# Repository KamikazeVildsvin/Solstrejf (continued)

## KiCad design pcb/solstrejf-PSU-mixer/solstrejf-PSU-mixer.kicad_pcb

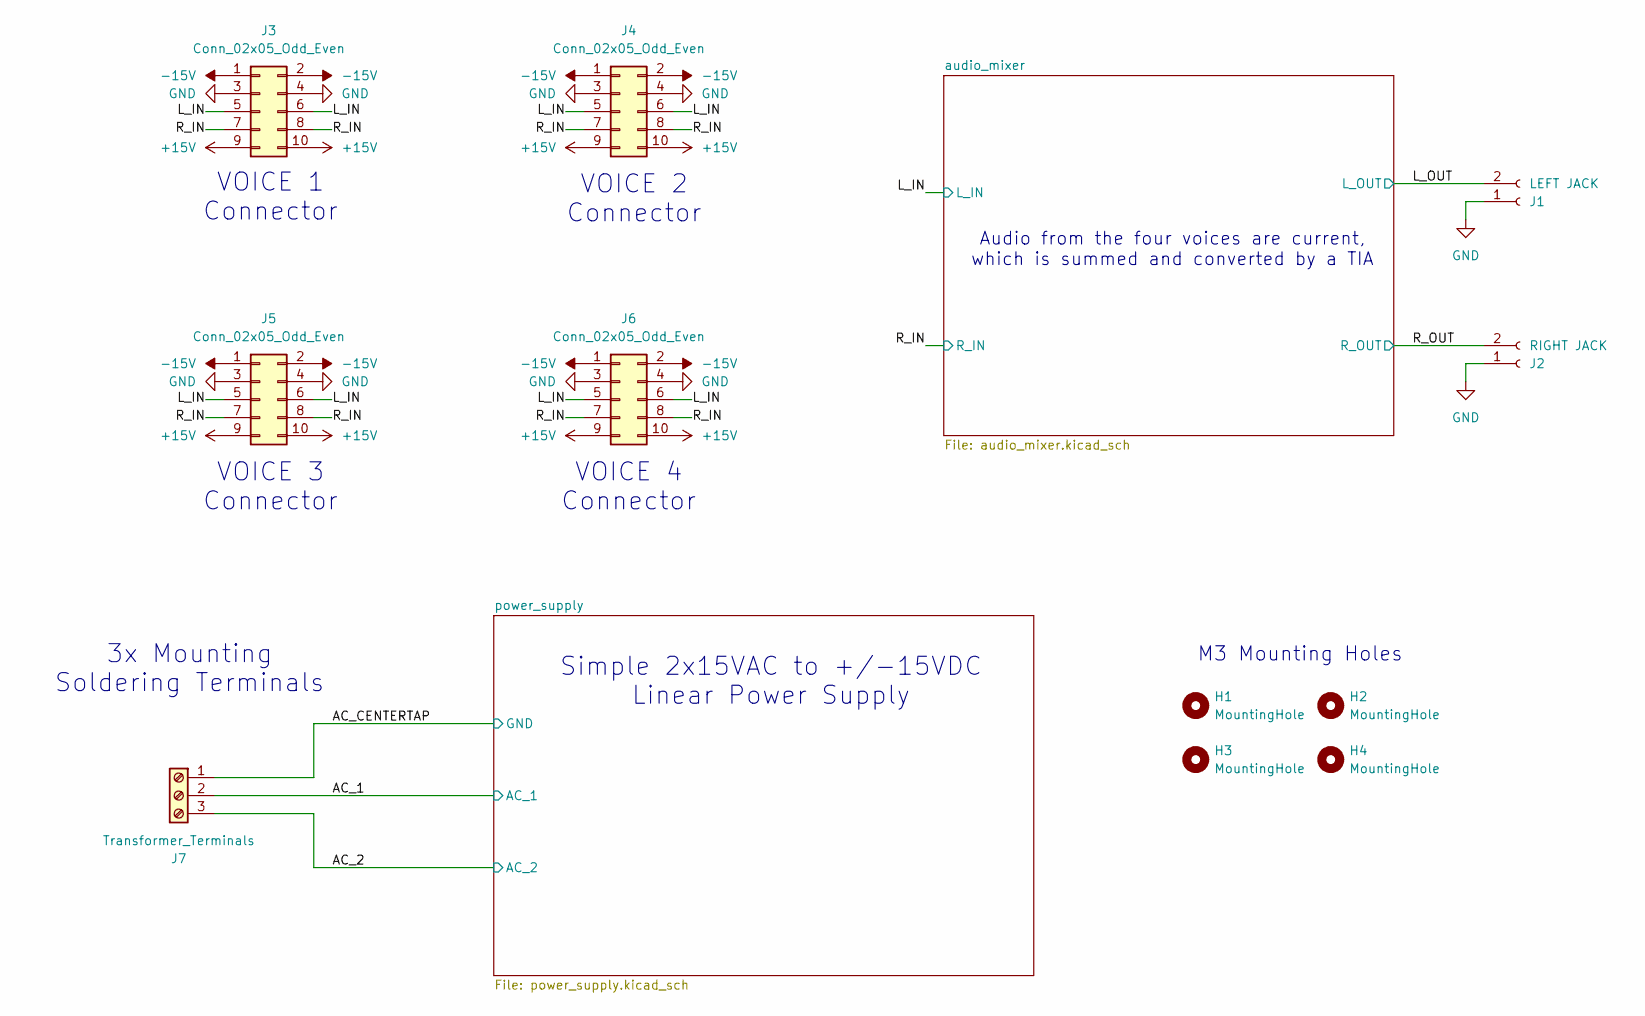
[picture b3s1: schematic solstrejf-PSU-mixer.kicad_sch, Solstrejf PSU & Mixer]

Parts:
H1, H2, H3, H4: MountingHole; MountingHole_3.2mm_M3_DIN965
J1: LEFT JACK; PinHeader_1x02_P2.54mm_Vertical
J2: RIGHT JACK; PinHeader_1x02_P2.54mm_Vertical
J3, J4, J5, J6: Conn_02x05_Odd_Even; IDC-Header_2x05_P2.54mm_Vertical
J7: Transformer_Terminals; SolderWire-0.5sqmm_1x03_P4.8mm_D0.9mm_OD2.3mm

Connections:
+15V: J3.9, J3.10, J4.9, J4.10, J5.9, J5.10, J6.9, J6.10; also elsewhere on the board
-15V: J3.1, J3.2, J4.1, J4.2, J5.1, J5.2, J6.1, J6.2; also elsewhere on the board
/AC_1: J7.2; also elsewhere on the board
/AC_2: J7.3; also elsewhere on the board
/L_IN: J3.5, J3.6, J4.5, J4.6, J5.5, J5.6, J6.5, J6.6; also elsewhere on the board
/L_OUT: J1.2; also elsewhere on the board
/R_IN: J3.7, J3.8, J4.7, J4.8, J5.7, J5.8, J6.7, J6.8; also elsewhere on the board
/R_OUT: J2.2; also elsewhere on the board
GND: J1.1, J2.1, J3.3, J3.4, J4.3, J4.4, J5.3, J5.4, J6.3, J6.4, J7.1; also elsewhere on the board

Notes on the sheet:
Audio from the four voices are current, which is summed and converted by a TIA
Simple 2x15VAC to +/-15VDC Linear Power Supply
M3 Mounting Holes
3x Mounting Soldering Terminals
VOICE 2 Connector
VOICE 1 Connector
VOICE 4 Connector
VOICE 3 Connector

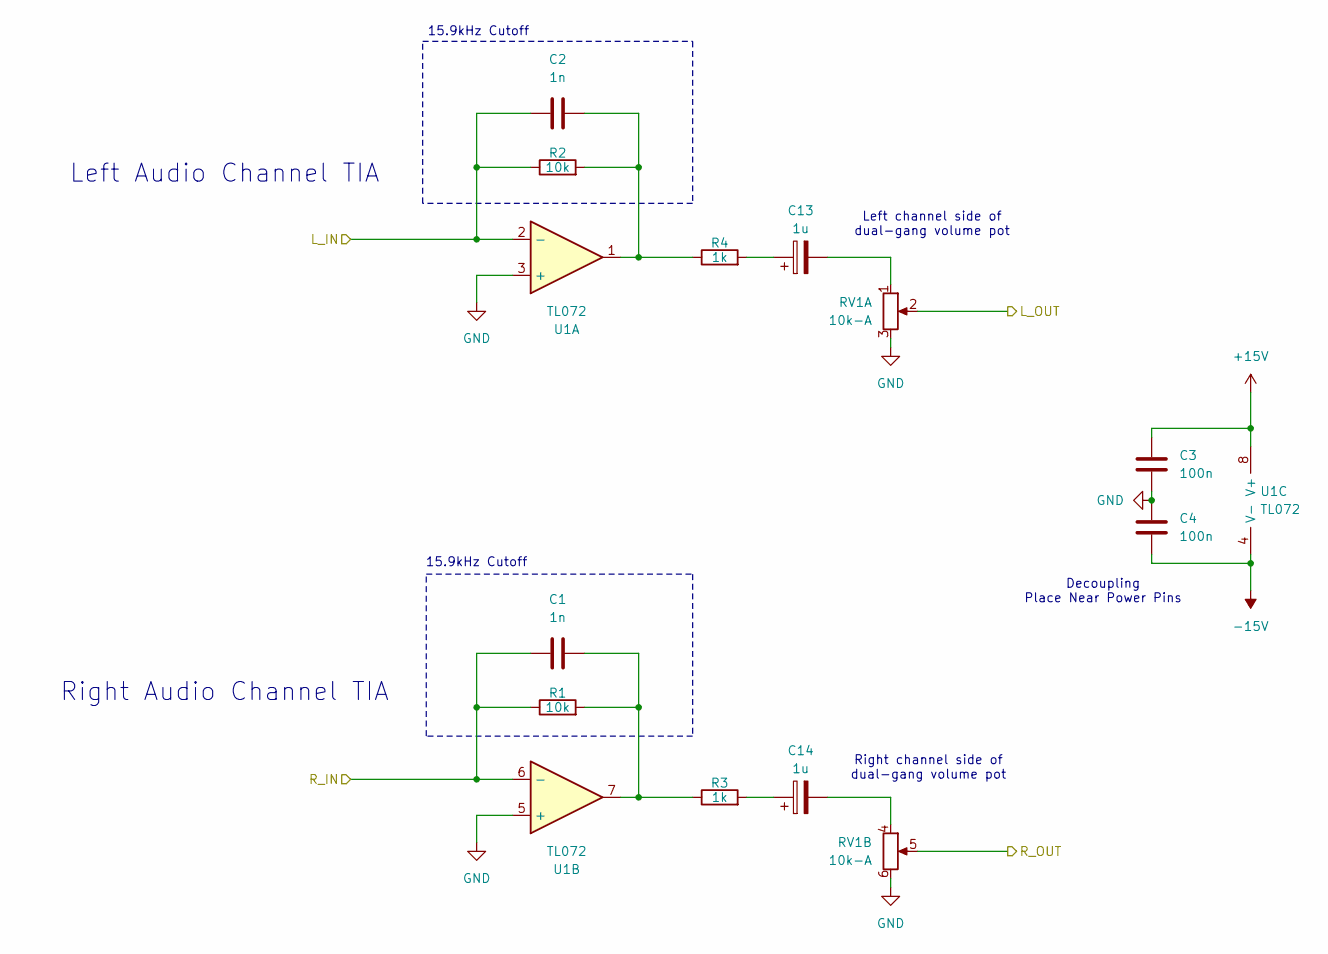
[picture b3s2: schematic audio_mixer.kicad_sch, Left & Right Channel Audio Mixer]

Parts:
C1, C2: 1n; C_Disc_D5.0mm_W2.5mm_P5.00mm
C3, C4: 100n; C_Disc_D5.0mm_W2.5mm_P5.00mm
C13, C14: 1u; CP_Radial_D5.0mm_P2.00mm
R1, R2: 10k; R_Axial_DIN0207_L6.3mm_D2.5mm_P10.16mm_Horizontal
R3, R4: 1k; R_Axial_DIN0207_L6.3mm_D2.5mm_P10.16mm_Horizontal
RV1: 10k-A; PinHeader_2x03_P2.54mm_Vertical
U1: TL072; DIP-8_W7.62mm

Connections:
+15V: C3.2, U1.8 (V+); also elsewhere on the board
-15V: C4.1, U1.4 (V-); also elsewhere on the board
/L_IN: C2.1, R2.1, U1.2 (-); also elsewhere on the board
/L_OUT: RV1.2; also elsewhere on the board
/R_IN: C1.1, R1.1, U1.6 (-); also elsewhere on the board
/R_OUT: RV1.5; also elsewhere on the board
GND: C3.1, C4.2, RV1.3, RV1.6, U1.3 (+), U1.5 (+); also elsewhere on the board
unnamed: C1.2, R1.2, R3.1, U1.7
unnamed: C2.2, R2.2, R4.1, U1.1
unnamed: C13.1, R4.2
unnamed: C13.2, RV1.1
unnamed: C14.1, R3.2
unnamed: C14.2, RV1.4

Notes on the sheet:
Decoupling Place Near Power Pins
Left Audio Channel TIA
15.9kHz Cutoff
Right Audio Channel TIA
Right channel side of dual-gang volume pot
Left channel side of dual-gang volume pot

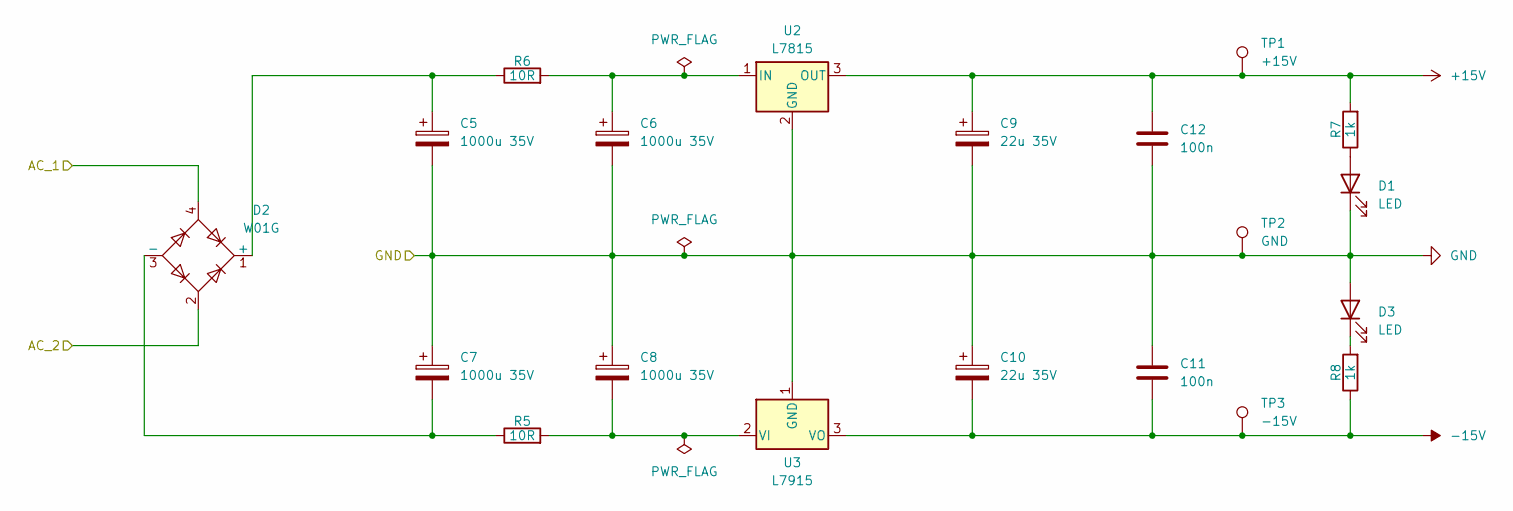
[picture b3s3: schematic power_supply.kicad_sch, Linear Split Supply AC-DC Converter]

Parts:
C5, C6, C7, C8: 1000u 35V; CP_Radial_D10.0mm_P5.00mm
C9, C10: 22u 35V; CP_Radial_D5.0mm_P2.00mm
C11, C12: 100n; C_Disc_D5.0mm_W2.5mm_P5.00mm
D1, D3: LED; LED_D5.0mm_FlatTop
D2: W01G; Diode_Bridge_Round_D9.8mm
R5, R6: 10R; R_Axial_DIN0207_L6.3mm_D2.5mm_P10.16mm_Horizontal
R7, R8: 1k; R_Axial_DIN0207_L6.3mm_D2.5mm_P10.16mm_Horizontal
TP1: +15V; PinHeader_1x01_P2.54mm_Vertical
TP2: GND; PinHeader_1x01_P2.54mm_Vertical
TP3: -15V; PinHeader_1x01_P2.54mm_Vertical
U2: L7815; TO-220-3_Vertical
U3: L7915; TO-220-3_Vertical

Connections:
+15V: C9.1, C12.2, R7.2, TP1.1, U2.3 (OUT); also elsewhere on the board
-15V: C10.2, C11.1, R8.1, TP3.1, U3.3 (VO); also elsewhere on the board
/AC_1: D2.4; also elsewhere on the board
/AC_2: D2.2; also elsewhere on the board
GND: C5.2, C6.2, C7.1, C8.1, C9.2, C10.1, C11.2, C12.1, D1.1 (K), D3.2 (A), TP2.1, U2.2 (GND), U3.1 (GND); also elsewhere on the board
unnamed: D1.2 (A), R7.1
unnamed: C5.1, D2.1 (+), R6.1
unnamed: C7.2, D2.3 (-), R5.1
unnamed: D3.1 (K), R8.2
unnamed: C6.1, R6.2, U2.1 (IN)
unnamed: C8.2, R5.2, U3.2 (VI)

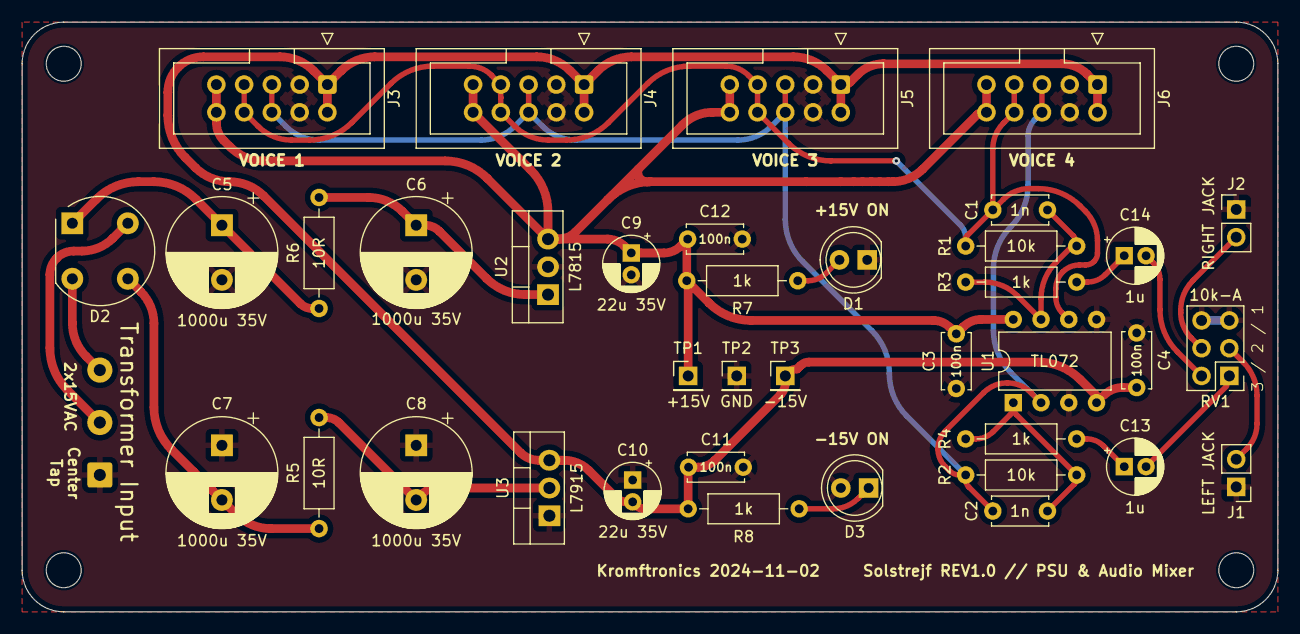
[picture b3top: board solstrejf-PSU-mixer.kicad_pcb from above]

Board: 2 copper layers, 114.9 x 54.0 mm, 43 parts (0 on the bottom side), 21 nets.

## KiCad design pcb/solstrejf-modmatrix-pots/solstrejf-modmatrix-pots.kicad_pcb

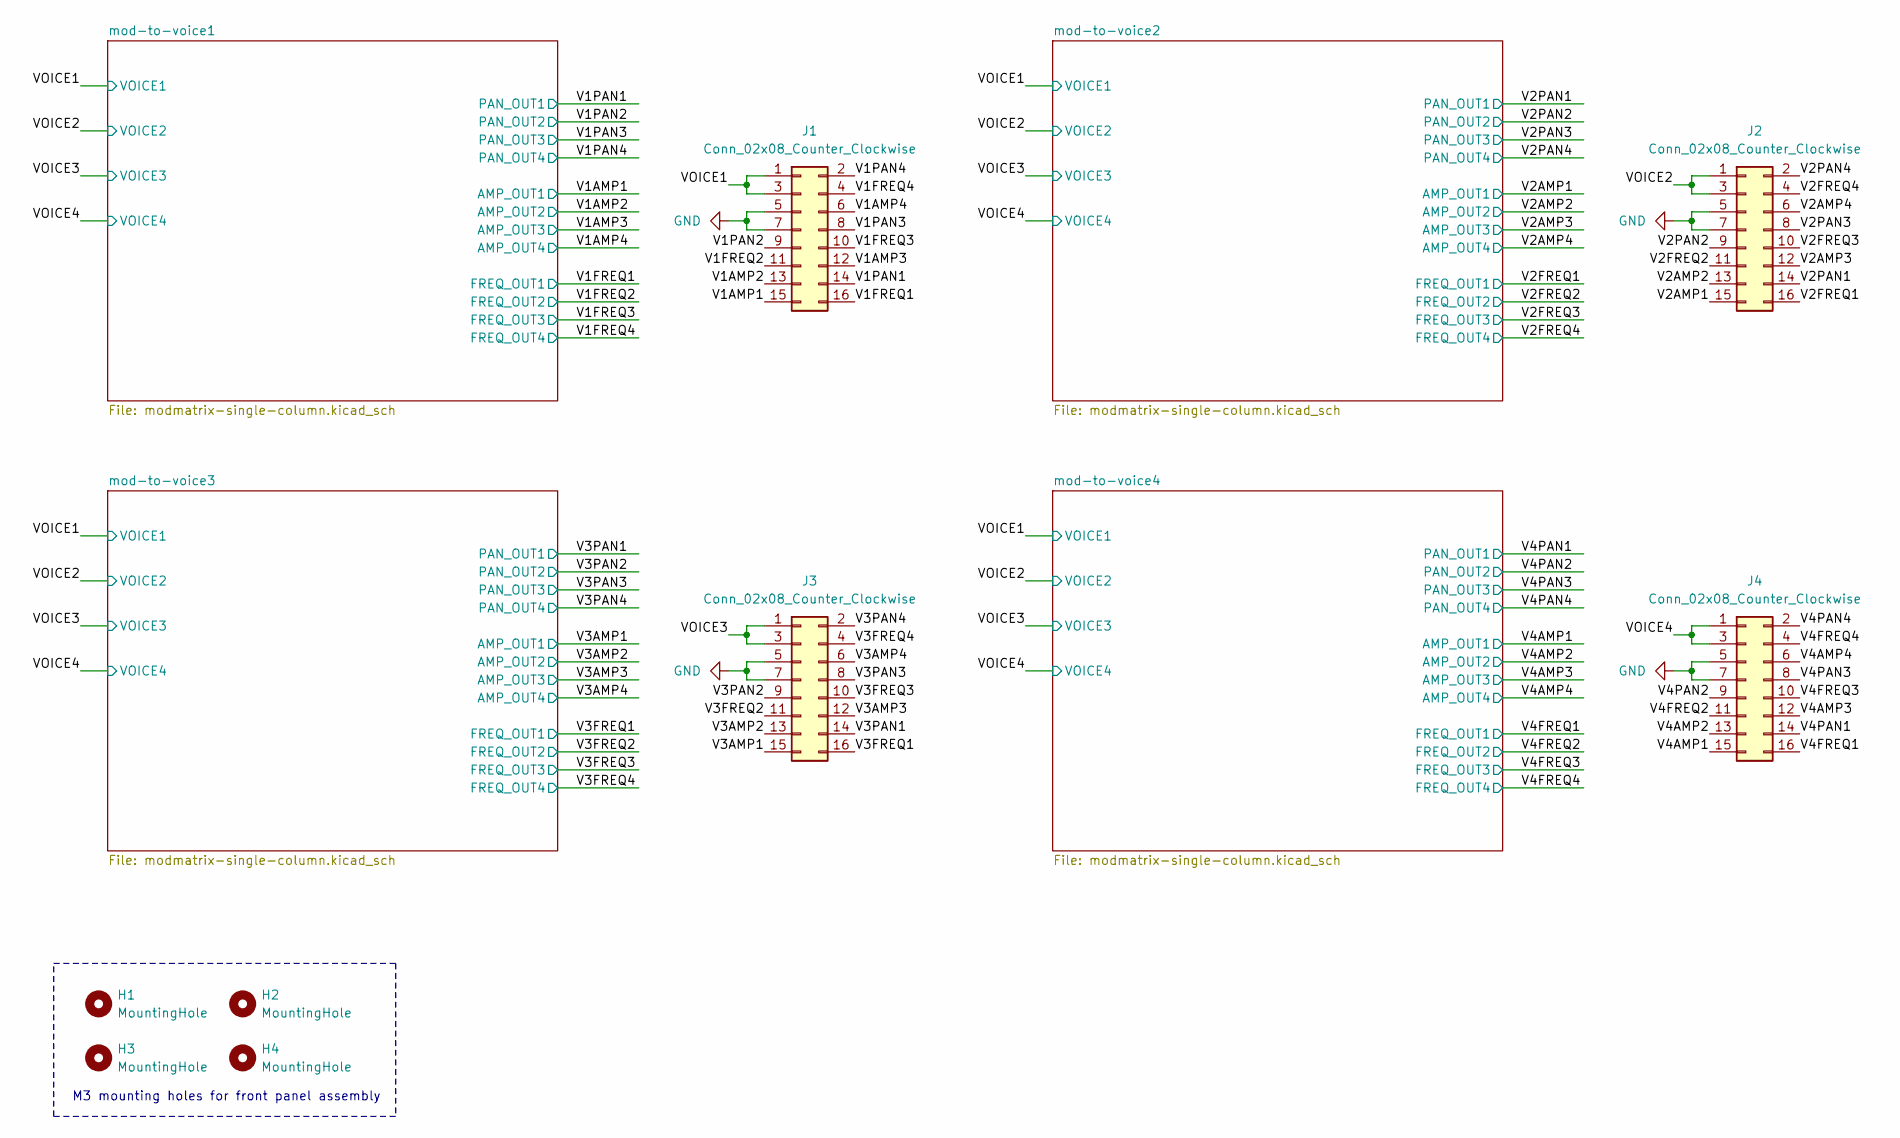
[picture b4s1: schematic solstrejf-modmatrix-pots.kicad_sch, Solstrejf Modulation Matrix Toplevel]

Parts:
H1, H2, H3, H4: MountingHole; MountingHole_3.2mm_M3_DIN965
J1, J2, J3, J4: Conn_02x08_Counter_Clockwise; IDC-Header_2x08_P2.54mm_Vertical

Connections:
/V1AMP1: J1.15; also elsewhere on the board
/V1AMP2: J1.13; also elsewhere on the board
/V1AMP3: J1.12; also elsewhere on the board
/V1AMP4: J1.6; also elsewhere on the board
/V1FREQ1: J1.16; also elsewhere on the board
/V1FREQ2: J1.11; also elsewhere on the board
/V1FREQ3: J1.10; also elsewhere on the board
/V1FREQ4: J1.4; also elsewhere on the board
/V1PAN1: J1.14; also elsewhere on the board
/V1PAN2: J1.9; also elsewhere on the board
/V1PAN3: J1.8; also elsewhere on the board
/V1PAN4: J1.2; also elsewhere on the board
/V2AMP1: J2.15; also elsewhere on the board
/V2AMP2: J2.13; also elsewhere on the board
/V2AMP3: J2.12; also elsewhere on the board
/V2AMP4: J2.6; also elsewhere on the board
/V2FREQ1: J2.16; also elsewhere on the board
/V2FREQ2: J2.11; also elsewhere on the board
/V2FREQ3: J2.10; also elsewhere on the board
/V2FREQ4: J2.4; also elsewhere on the board
/V2PAN1: J2.14; also elsewhere on the board
/V2PAN2: J2.9; also elsewhere on the board
/V2PAN3: J2.8; also elsewhere on the board
/V2PAN4: J2.2; also elsewhere on the board
/V3AMP1: J3.15; also elsewhere on the board
/V3AMP2: J3.13; also elsewhere on the board
/V3AMP3: J3.12; also elsewhere on the board
/V3AMP4: J3.6; also elsewhere on the board
/V3FREQ1: J3.16; also elsewhere on the board
/V3FREQ2: J3.11; also elsewhere on the board
/V3FREQ3: J3.10; also elsewhere on the board
/V3FREQ4: J3.4; also elsewhere on the board
/V3PAN1: J3.14; also elsewhere on the board
/V3PAN2: J3.9; also elsewhere on the board
/V3PAN3: J3.8; also elsewhere on the board
/V3PAN4: J3.2; also elsewhere on the board
/V4AMP1: J4.15; also elsewhere on the board
/V4AMP2: J4.13; also elsewhere on the board
/V4AMP3: J4.12; also elsewhere on the board
/V4AMP4: J4.6; also elsewhere on the board
/V4FREQ1: J4.16; also elsewhere on the board
/V4FREQ2: J4.11; also elsewhere on the board
/V4FREQ3: J4.10; also elsewhere on the board
/V4FREQ4: J4.4; also elsewhere on the board
/V4PAN1: J4.14; also elsewhere on the board
/V4PAN2: J4.9; also elsewhere on the board
/V4PAN3: J4.8; also elsewhere on the board
/V4PAN4: J4.2; also elsewhere on the board
/VOICE1: J1.1, J1.3; also elsewhere on the board
/VOICE2: J2.1, J2.3; also elsewhere on the board
/VOICE3: J3.1, J3.3; also elsewhere on the board
/VOICE4: J4.1, J4.3; also elsewhere on the board
GND: J1.5, J1.7, J2.5, J2.7, J3.5, J3.7, J4.5, J4.7; also elsewhere on the board

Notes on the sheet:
M3 mounting holes for front panel assembly

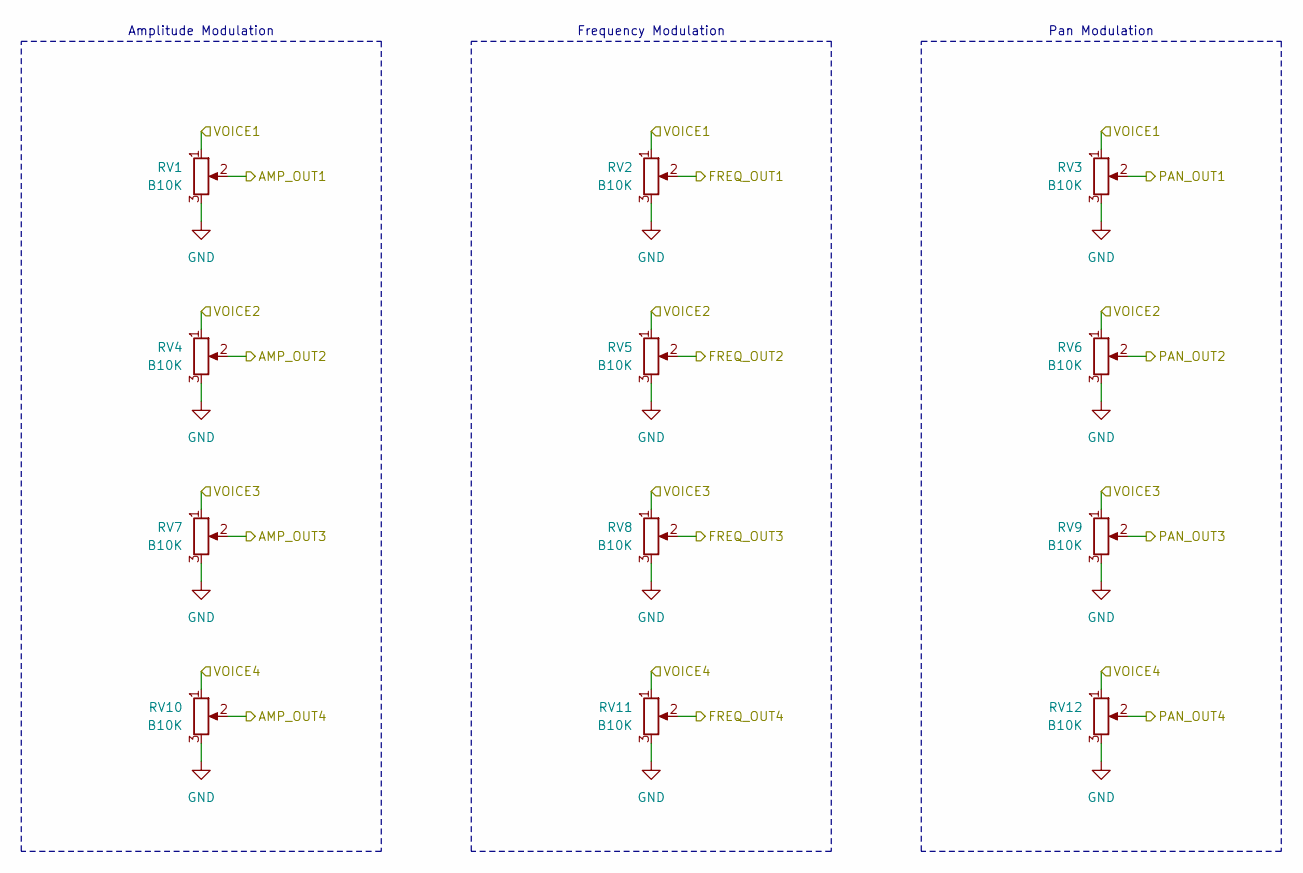
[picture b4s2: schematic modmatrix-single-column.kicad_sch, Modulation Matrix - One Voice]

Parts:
RV1, RV2, RV3, RV4, RV5, RV6, RV7, RV8, RV9, RV10, RV11, RV12: B10K; Potentiometer_Alpha_slide_pot_30mm

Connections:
/V1AMP1: RV1.2; also elsewhere on the board
/V1AMP2: RV4.2; also elsewhere on the board
/V1AMP3: RV7.2; also elsewhere on the board
/V1AMP4: RV10.2; also elsewhere on the board
/V1FREQ1: RV2.2; also elsewhere on the board
/V1FREQ2: RV5.2; also elsewhere on the board
/V1FREQ3: RV8.2; also elsewhere on the board
/V1FREQ4: RV11.2; also elsewhere on the board
/V1PAN1: RV3.2; also elsewhere on the board
/V1PAN2: RV6.2; also elsewhere on the board
/V1PAN3: RV9.2; also elsewhere on the board
/V1PAN4: RV12.2; also elsewhere on the board
/VOICE1: RV1.1, RV2.1, RV3.1; also elsewhere on the board
/VOICE2: RV4.1, RV5.1, RV6.1; also elsewhere on the board
/VOICE3: RV7.1, RV8.1, RV9.1; also elsewhere on the board
/VOICE4: RV10.1, RV11.1, RV12.1; also elsewhere on the board
GND: RV1.3, RV2.3, RV3.3, RV4.3, RV5.3, RV6.3, RV7.3, RV8.3, RV9.3, RV10.3, RV11.3, RV12.3; also elsewhere on the board

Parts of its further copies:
RV13, RV14, RV15, RV16, RV17, RV18, RV19, RV20, RV21, RV22, RV23, RV24, RV25, RV26, RV27, RV28, RV29, RV30, RV31, RV32, RV33, RV34, RV35, RV36, RV37, RV38, RV39, RV40, RV41, RV42, RV43, RV44, RV45, RV46, RV47, RV48: B10K; Potentiometer_Alpha_slide_pot_30mm

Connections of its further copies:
/V2AMP1: RV13.2; also elsewhere on the board
/V2AMP2: RV16.2; also elsewhere on the board
/V2AMP3: RV19.2; also elsewhere on the board
/V2AMP4: RV22.2; also elsewhere on the board
/V2FREQ1: RV14.2; also elsewhere on the board
/V2FREQ2: RV17.2; also elsewhere on the board
/V2FREQ3: RV20.2; also elsewhere on the board
/V2FREQ4: RV23.2; also elsewhere on the board
/V2PAN1: RV15.2; also elsewhere on the board
/V2PAN2: RV18.2; also elsewhere on the board
/V2PAN3: RV21.2; also elsewhere on the board
/V2PAN4: RV24.2; also elsewhere on the board
/V3AMP1: RV25.2; also elsewhere on the board
/V3AMP2: RV28.2; also elsewhere on the board
/V3AMP3: RV31.2; also elsewhere on the board
/V3AMP4: RV34.2; also elsewhere on the board
/V3FREQ1: RV26.2; also elsewhere on the board
/V3FREQ2: RV29.2; also elsewhere on the board
/V3FREQ3: RV32.2; also elsewhere on the board
/V3FREQ4: RV35.2; also elsewhere on the board
/V3PAN1: RV27.2; also elsewhere on the board
/V3PAN2: RV30.2; also elsewhere on the board
/V3PAN3: RV33.2; also elsewhere on the board
/V3PAN4: RV36.2; also elsewhere on the board
/V4AMP1: RV37.2; also elsewhere on the board
/V4AMP2: RV40.2; also elsewhere on the board
/V4AMP3: RV43.2; also elsewhere on the board
/V4AMP4: RV46.2; also elsewhere on the board
/V4FREQ1: RV38.2; also elsewhere on the board
/V4FREQ2: RV41.2; also elsewhere on the board
/V4FREQ3: RV44.2; also elsewhere on the board
/V4FREQ4: RV47.2; also elsewhere on the board
/V4PAN1: RV39.2; also elsewhere on the board
/V4PAN2: RV42.2; also elsewhere on the board
/V4PAN3: RV45.2; also elsewhere on the board
/V4PAN4: RV48.2; also elsewhere on the board
/VOICE1: RV13.1, RV14.1, RV15.1, RV25.1, RV26.1, RV27.1, RV37.1, RV38.1, RV39.1; also elsewhere on the board
/VOICE2: RV16.1, RV17.1, RV18.1, RV28.1, RV29.1, RV30.1, RV40.1, RV41.1, RV42.1; also elsewhere on the board
/VOICE3: RV19.1, RV20.1, RV21.1, RV31.1, RV32.1, RV33.1, RV43.1, RV44.1, RV45.1; also elsewhere on the board
/VOICE4: RV22.1, RV23.1, RV24.1, RV34.1, RV35.1, RV36.1, RV46.1, RV47.1, RV48.1; also elsewhere on the board
GND: RV13.3, RV14.3, RV15.3, RV16.3, RV17.3, RV18.3, RV19.3, RV20.3, RV21.3, RV22.3, RV23.3, RV24.3, RV25.3, RV26.3, RV27.3, RV28.3, RV29.3, RV30.3, RV31.3, RV32.3, RV33.3, RV34.3, RV35.3, RV36.3, RV37.3, RV38.3, RV39.3, RV40.3, RV41.3, RV42.3, RV43.3, RV44.3, RV45.3, RV46.3, RV47.3, RV48.3; also elsewhere on the board

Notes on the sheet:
Pan Modulation
Amplitude Modulation
Frequency Modulation

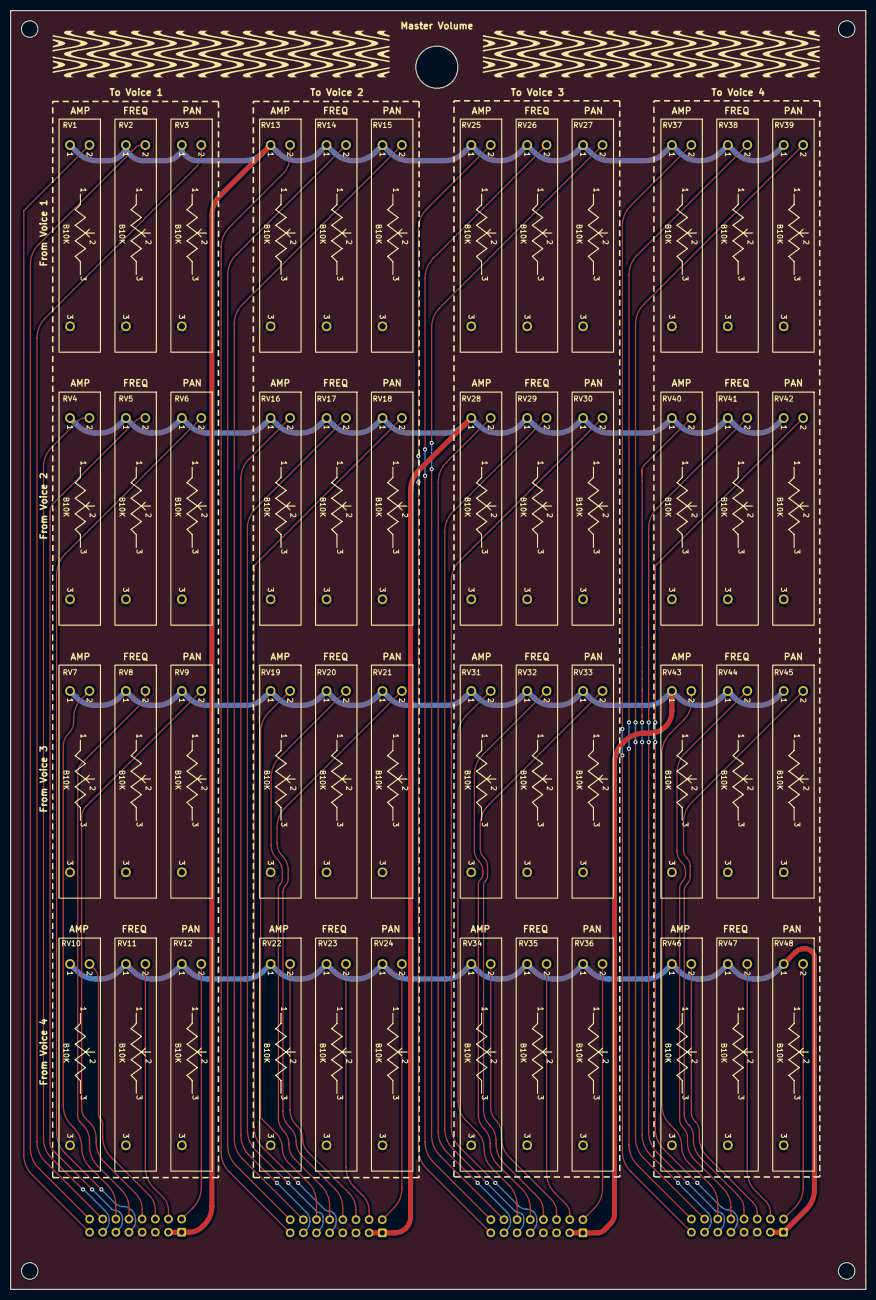
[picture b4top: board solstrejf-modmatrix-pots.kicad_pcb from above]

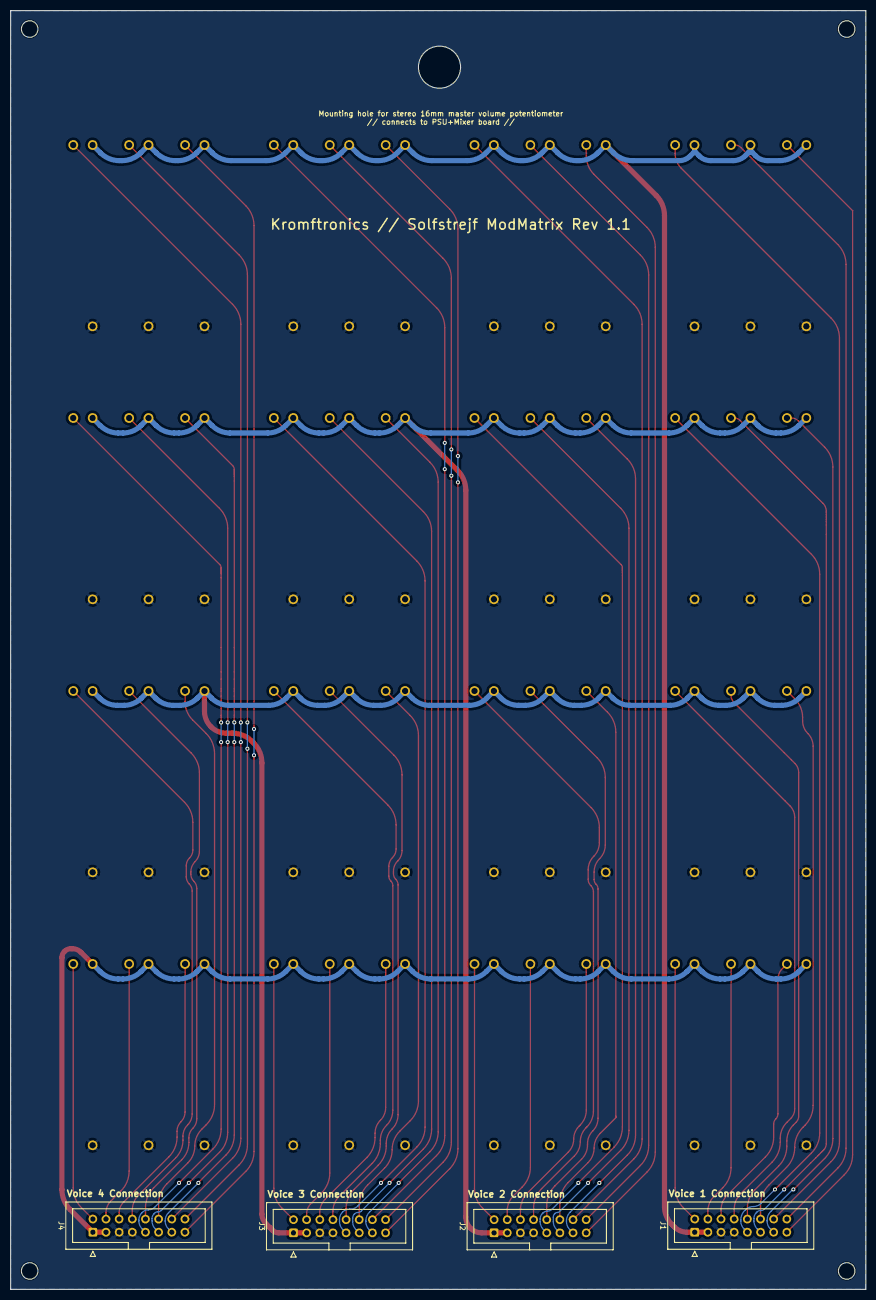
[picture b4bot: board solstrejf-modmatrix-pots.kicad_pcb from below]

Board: 2 copper layers, 165.1 x 246.9 mm, 56 parts (4 on the bottom side), 53 nets.

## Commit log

2024-04-25 added README
2024-04-25 added .gitignore and remove .DS_Store files
2024-04-25 removed backup folder from modmatrix pcb and added to .gitignore
2024-04-28 Create LICENSE
2024-04-28 Update LICENSE
2024-04-28 updated .gitignore
2024-05-02 updated pcb layout
2024-05-05 Finished routing of modmatrix!
2024-05-05 removed .log files from kicad and added to .gitignore
2024-05-17 updated .gitignore. Added silkscreen text to pcb.
2024-05-20 created new LTspice files dir. added .net and .raw to .gitignore. Created VCA-to-PAN circuit simulations.
2024-05-20 moved dirs to LTspice dir.
2024-05-23 created the PSU and L/R audio mixer KiCad project. Schematic Done. PCB footprints importet
2024-06-13 created an LTspice schematic for testing the output mixer TIA.
2024-06-13 updated KiCad schematic and PCB with the new changes added to the TIA after LTspice simulations.
2024-07-12 Added Mod-matric PCB renders and updated README with pictures and more description.
2024-07-12 made first attempt of a PCB layout onf the PSU/mixer. No routing performed. Minor updates to schematic, including mounting holes.
2024-07-15 routing of PSU/mixer done! Minor schematic updates. Added gerber production files to .gitignore.
2024-07-15 added PSU/audio-mixer PCB images and renders to README
2024-08-06 Updated LTspice files and started on VCA-cv-mixer Updated all LTspice to use an .include statement for the lm24x opamp. Started to work on the VCA CV limiting mixer. This also includes a Jupyter note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
2024-08-21 Added kromftronics custom kicad files as submodule. Updated modmatrix KiCad project to use the submodule.
2024-08-21 Update README with description of recursive import of submodules
2024-08-21 Added initial voice board schematic template with new AS3372E symbol.
2024-08-21 added modified symbols library submodule update
2024-08-21 Added lastest KiCad library commit
2024-08-24 Updated fonts in PSU+mixer schematic. Added a print of the PSU+mixer schemtic in new directory.
2024-08-24 Inital draft of the voice board power supplys and core.
2024-08-24 Updated sheet titles in modulation matrix and exported current rev1.0 schematic
2024-08-24 Created hierarchical pins for the three CV sub-circuits and added the rest of the core circuitry for the voice board.
2024-08-25 Updated LTspice simulation of output TIA with decrease volume pot for 15.92Hz highpass frequency. Updated KiCad and images with the same change.
2024-08-27 created schematic for CV circuits: PAN, VCA, and FREQ. Created a new symbol for the ONESHOT envelope generator
2024-08-27 LTspice files: updated PAN cv schematic. Added new schematic for the PDM filtering in the ONESHOT envelope generator.
2024-08-31 created voice board front panel KiCad projects. Made some updates in the Kromftronics KiCad repo.
2024-09-01 updated Kromftronics submodule name and edited path in all PCB projects. Added work-in-progress for the front-panel PCB and the small updates in the voice-board schematic
2024-09-01 Updated modmatrix project: added more silkscreen and removed rounded edges. Stored 3D models in mod-matrix project for better portability. Added new images of the current state of the mod-matrix PCB.
2024-09-01 Rotated mod-matrix image
2024-09-01 Updated voice board front-panel and mod-matrix
    Created new dimensions to get a better physical layout of the 4x voice board control panels and the mod-matrix.
    Exported .wrl 3D models of voice board front-panel and mod-matrix to create a MeshLab view.
    Added MeshLab project files and new images aswell.
2024-09-02 Plotted latest schematic
2024-09-02 Updated frequency CV summer circuit to use +/-12V local regulator instead of +/15V. Updated LTspice, notebooks, and KiCad project
2024-09-02 Added plotting path for the schematic of the front-panel KiCad project
2024-09-07 Updated mod-matrix PCB to have a hole for master volume pot
    Added a M8 hole in the mod-matrix PCB to be able to attach the stereo master volume control.
    Updated the images of the mod-matrix and the meshlab render.
2024-10-20 Started layout on voice board. Work-in-progress.
2024-10-21 Layout work-in-progress..
2024-10-22 Added M3 mounting holes to schematic/PCB and worked on power/regulator layout
2024-10-26 Update .gitignore to disregard .zip files (e.g. production outputs of the gerber file generations)
2024-10-27 Finish layout of the voice board. Included 3D renders in README.
2024-10-28 Found an error in the front panel where the volume pot was inverted. Updated the schematics of the voice board core and front panel.
2024-10-28 Updated voice panel PCB image
2024-10-28 Rotated image
2024-11-02 Created ibom for voice board front panel
2024-11-02 Created ibom for the voice board.
2024-11-02 Created ibom for the PSU+mixer board
2024-11-02 Updated potentiometer value from B10k to B10K in order for all of the slide pots to have the same value in the BOM. Generated ibom for the mod-matrix board.
2024-11-02 Updated README to include the ibom's
2024-11-02 Updated values of electrolytic caps on voice board to match in the ibom.
2024-11-18 Fixed a footprint error in the Alpha slide pot. Pad holes were 0.7mm in diameter, but needed to be 1mm. Updated this in mod-matrix and front panel control.
2024-11-18 Created rev1.1 for mod-matrix and voice board front panel. Exported a new ibom for both of them.
2024-11-18 Added text in README about PCBWay sponsorship. Added .vscode to .gitignore
2024-11-18 Small typo in README
2024-11-25 updated Alpha slide pot footprint to have 1.2mm drill hole diameter to match the 1mm pins
2024-11-25 Added the correct version of the KiCad footprint library with the modified Alpha slide pot footprint
2024-12-22 Added variable revision and date silkscreen prints for all four boards of Solstrejf
    This means that the revision and issue date that is set in the page setup
    of the PCB's will be update on the silscreen automatically so I don't forget
    to update the revsions on the silkscreen :')
2025-02-28 Saved Solstrejf Kicad files in 9.0 format
2025-03-01 Created rev1.1 of Solstref voice board. Updated value of some resistors (66k->68k). Exported new ibom and schematic.
2025-03-02 Updated resistor value in VCF CV circuit. Generated new ibom and schematic.
2025-03-08 Updated two capacitor values in voice board power section 330n->100n. Updated Schematic and created new IBOM.
2025-03-13 saved voice board project file.
2025-11-15 updated frontpanel to rev2
    - added a external trigger input for PIR motion sensor
    - added a 0-5V 1V/oct cv input to the frequency cv
    - PCB DRC clean
2025-11-16 generated new ibom for rev2
2026-01-02 updated frontpanel resistor value and added 3D renders
2026-01-29 updated frontpanel trig opamp output resistor due
    - the weak pull-up on the ONESHOT env cause errors with creating zeros
